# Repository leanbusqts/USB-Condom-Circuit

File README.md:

# USB-Condom-Circuit

Circuito en Autodesk Eagle, de protección de carga USB. 

Autodesk Eagle circuit, USB charging protection.

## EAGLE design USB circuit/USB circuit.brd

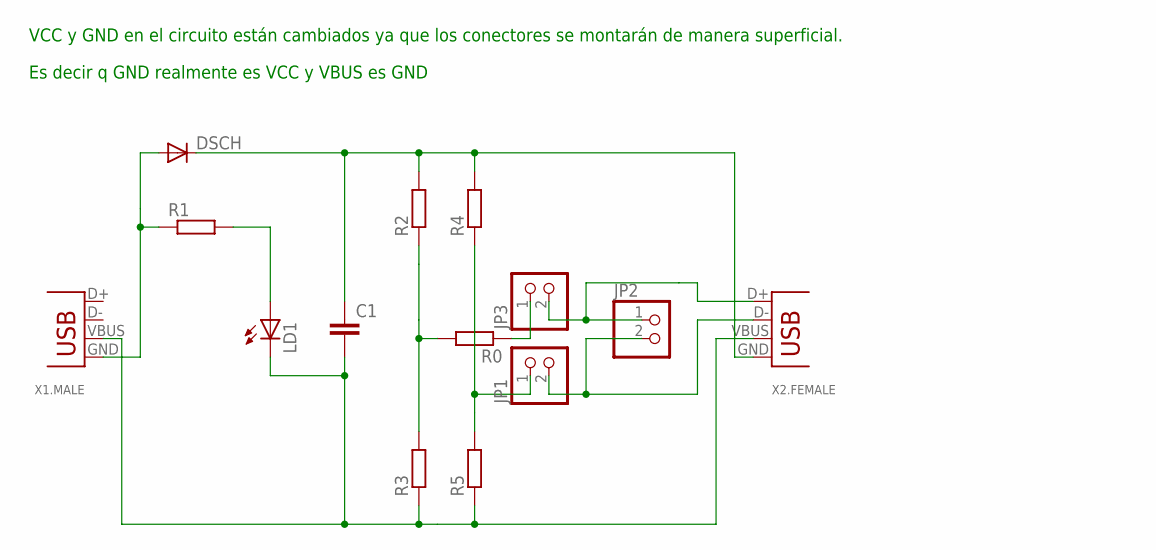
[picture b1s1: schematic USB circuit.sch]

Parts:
C1: C-EUC1812; C1812
DSCH: DIODE-SOD123; SOD123
JP1, JP2, JP3: PINHD-1X2_2.54; 1X02
LD1: LEDCHIPLED_1206; CHIPLED_1206
R0, R1, R2, R3, R4, R5: R-EU_R1206; R1206
X1.MALE, X2.FEMALE: USB-A-H

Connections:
GND: C1.2, LD1.C, R3.1, R5.1, X1.MALE.VBUS, X2.FEMALE.VBUS
unnamed: JP1.1, R4.1, R5.2
unnamed: C1.1, DSCH.C, R2.2, R4.2, X2.FEMALE.GND
unnamed: LD1.A, R1.2
unnamed: JP1.2, JP2.2, X2.FEMALE.D-
unnamed: JP3.1, R0.1
unnamed: R0.2, R2.1, R3.2
unnamed: JP2.1, JP3.2, X2.FEMALE.D+
VCC: DSCH.A, R1.1, X1.MALE.GND

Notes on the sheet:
VCC y GND en el circuito están cambiados ya que los conectores se montarán de manera superficial.
Es decir q GND realmente es VCC y VBUS es GND

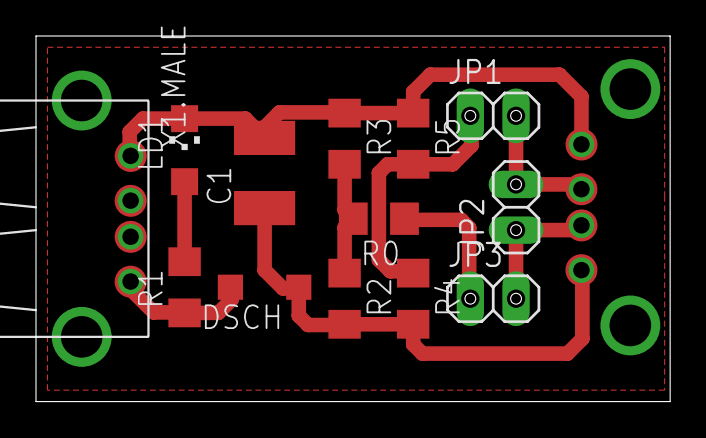
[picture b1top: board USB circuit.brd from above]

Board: 2 copper layers, 35.2 x 20.3 mm, 14 parts (1 on the bottom side), 9 nets.

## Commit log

2020-01-04 Readme file.
